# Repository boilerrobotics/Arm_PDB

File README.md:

# Arm_PDB
Power Distribution Board for our Robotic Arm
$ git init
$ git add -A
$ git commit -m 'Added my project'
$ git remote add origin git@github.com:MaggieM-Code/Power_Distribution_Board.git
$ git push -u -f origin main

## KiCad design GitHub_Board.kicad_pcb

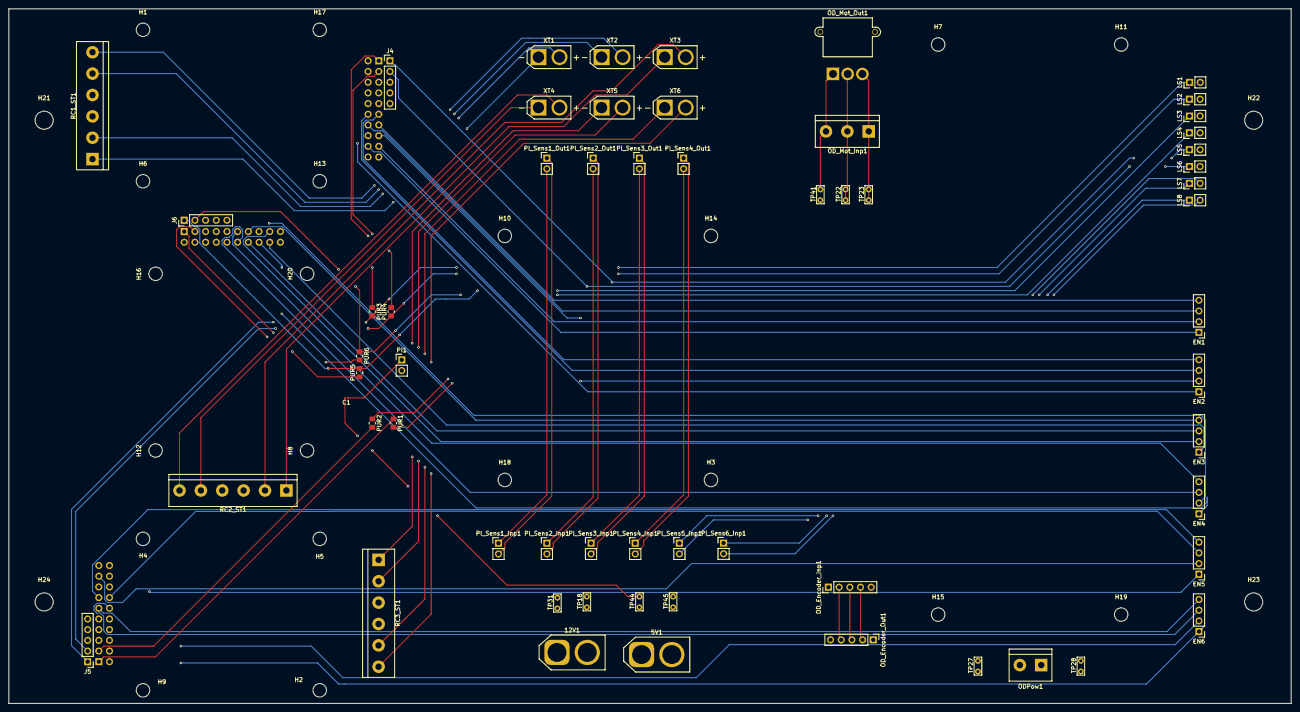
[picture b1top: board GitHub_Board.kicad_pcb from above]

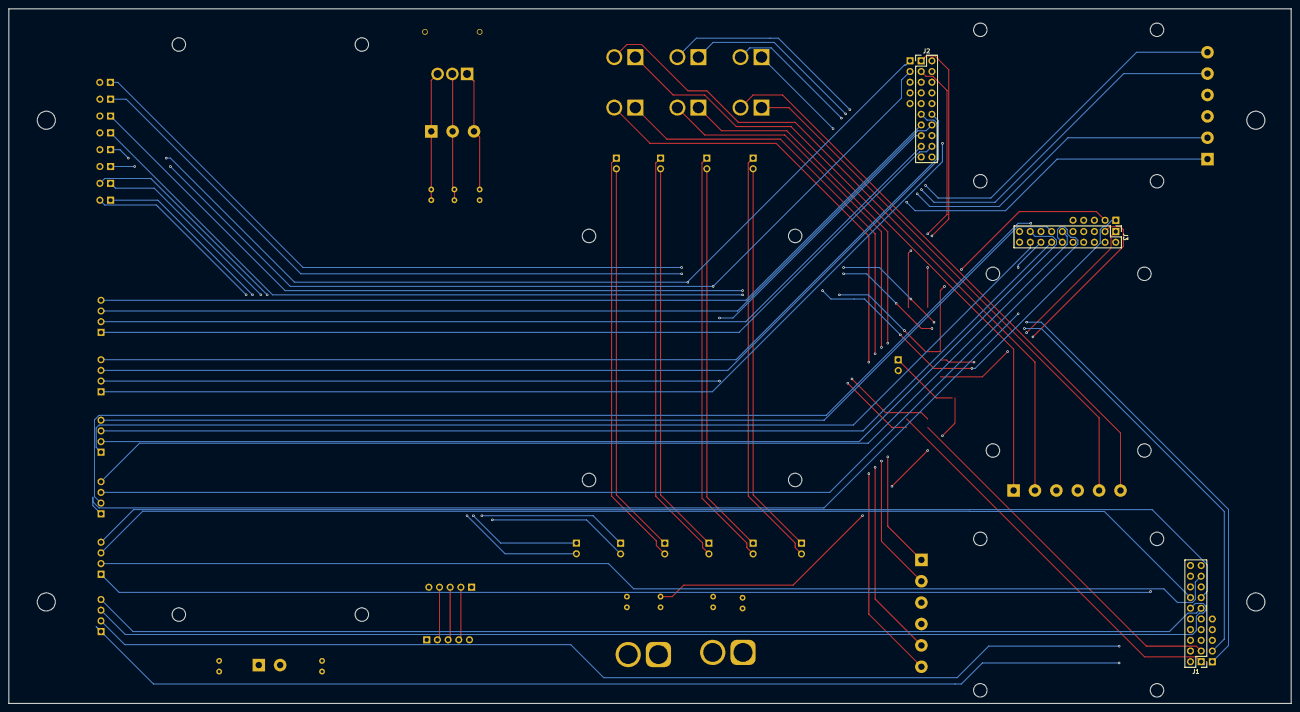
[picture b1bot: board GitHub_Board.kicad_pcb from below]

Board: 6 copper layers, 304.8 x 165.1 mm, 87 parts (3 on the bottom side), 70 nets.

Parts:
5V1, 12V1: Conn_01x02_Male; AMASS_XT60-M_1x02_P7.20mm_Vertical
C1: C; C_0201_0603Metric
EN1, EN2, EN3, EN4, EN5, EN6: Conn_01x04; PinHeader_1x04_P2.54mm_Vertical
H1, H2, H3, H4, H5, H6, H7, H8, H9, H10, H11, H12, H13, H14, H15, H16, H17, H18, H19, H20: MountingHole; MountingHole_3.2mm_M3
H21, H22, H23, H24: MountingHole; MountingHole_4.3mm_M4
J1, J2, J3: Conn_02x10_Top_Bottom; PinHeader_2x10_P2.54mm_Vertical
J4, J5, J6: Conn_01x05; PinHeader_1x05_P2.54mm_Vertical
LS1, LS2, LS3, LS4, LS5, LS6, LS7, LS8: Conn_02x01; PinHeader_1x02_P2.54mm_Vertical
ODPow1: Screw_Terminal_01x02; TerminalBlock_bornier-2_P5.08mm
OD_Encoder_Inp1: Conn_01x04; PinHeader_1x05_P2.54mm_Vertical
OD_Encoder_Out1: Conn_01x04; PinHeader_1x05_P2.54mm_Vertical
OD_Mot_Inp1: Screw_Terminal_01x03; TerminalBlock_bornier-3_P5.08mm
OD_Mot_Out1: Conn_01x03; AMASS_MR30PW-M_1x03_P3.50mm_Horizontal
PI1: Conn_01x02; PinHeader_1x02_P2.54mm_Vertical
PI_Sens1_Inp1, PI_Sens1_Out1, PI_Sens2_Inp1, PI_Sens2_Out1, PI_Sens3_Inp1, PI_Sens3_Out1, PI_Sens4_Inp1, PI_Sens4_Out1, PI_Sens5_Inp1, PI_Sens6_Inp1: Conn_01x02; PinHeader_1x02_P2.54mm_Vertical
PUR1, PUR2, PUR3, PUR4, PUR5, PUR6: R_US; R_0805_2012Metric_Pad1.20x1.40mm_HandSolder
RC1_ST1, RC2_ST1, RC3_ST1: Screw_Terminal_01x06; TerminalBlock_bornier-6_P5.08mm
TP18, TP22, TP23, TP27, TP28, TP31, TP41, TP44, TP45: TestPoint_Probe; TestPoint_Bridge_Pitch2.54mm_Drill0.7mm
XT1, XT2, XT3, XT4, XT5, XT6: Conn_01x02_Male; AMASS_XT30U-M_1x02_P5.0mm_Vertical

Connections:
+5V: 5V1.1, C1.2, OD_Encoder_Inp1.5, OD_Encoder_Out1.1, TP44.1
+12V: 12V1.1, ODPow1.2, RC1_ST1.3, RC2_ST1.3, RC3_ST1.3, TP27.1, TP31.1
/A: OD_Mot_Inp1.3, OD_Mot_Out1.1, TP41.1
/B: OD_Mot_Inp1.2, OD_Mot_Out1.2, TP22.1
/C: OD_Mot_Inp1.1, OD_Mot_Out1.3, TP23.1
/EN1+: EN1.2, J2.17
/EN1-: EN1.1, J2.18
/EN1a: EN1.4, J2.13
/EN1b: EN1.3, J2.14
/EN2+: EN2.2, J2.15
/EN2-: EN2.1, J2.16
/EN2a: EN2.4, J2.11
/EN2b: EN2.3, J2.12
/EN3+: EN3.2, J3.17
/EN3-: EN3.1, J3.18
/EN3a: EN3.4, J3.13
/EN3b: EN3.3, J3.14
/EN4+: EN4.2, J3.15
/EN4-: EN4.1, J3.16
/EN4a: EN4.4, J3.11
/EN4b: EN4.3, J3.12
/EN5+: EN5.2, J1.17
/EN5-: EN5.1, J1.18
/EN5a: EN5.4, J1.13
/EN5b: EN5.3, J1.14
/EN6+: EN6.2, J1.15
/EN6-: EN6.1, J1.16
/EN6a: EN6.4, J1.11
/EN6b: EN6.3, J1.12
/EN_A: OD_Encoder_Inp1.4, OD_Encoder_Out1.2
/EN_B: OD_Encoder_Inp1.3, OD_Encoder_Out1.3
/EN_C: OD_Encoder_Inp1.2, OD_Encoder_Out1.4
/LS1: J5.1, LS1.1, PUR3.2
/LS2: J5.2, LS2.1, PUR4.1
/LS3: J6.1, LS3.1, PUR5.2
/LS4: J6.2, LS4.1, PUR6.1
/LS5: J4.1, LS5.1, PUR1.2
/LS6: J4.2, LS6.1, PUR2.1
/LS7a: LS7.1, PI_Sens5_Inp1.1
/LS7b: LS7.2, PI_Sens5_Inp1.2
/LS8a: LS8.1, PI_Sens6_Inp1.1
/LS8b: LS8.2, PI_Sens6_Inp1.2
/Sens1_1: PI_Sens1_Inp1.2, PI_Sens1_Out1.1
/Sens1_2: PI_Sens1_Inp1.1, PI_Sens1_Out1.2
/Sens2_1: PI_Sens2_Inp1.2, PI_Sens2_Out1.1
/Sens2_2: PI_Sens2_Inp1.1, PI_Sens2_Out1.2
/Sens3_1: PI_Sens3_Inp1.2, PI_Sens3_Out1.1
/Sens3_2: PI_Sens3_Inp1.1, PI_Sens3_Out1.2
/Sens4_1: PI_Sens4_Inp1.2, PI_Sens4_Out1.1
/Sens4_2: PI_Sens4_Inp1.1, PI_Sens4_Out1.2
/XT301+: RC1_ST1.1, XT1.1
/XT301-: RC1_ST1.2, XT1.2
/XT302+: RC1_ST1.5, XT2.1
/XT302-: RC1_ST1.6, XT2.2
/XT303+: RC2_ST1.1, XT3.1
/XT303-: RC2_ST1.2, XT3.2
/XT304+: RC2_ST1.5, XT4.1
/XT304-: RC2_ST1.6, XT4.2
/XT305+: RC3_ST1.1, XT5.1
/XT305-: RC3_ST1.2, XT5.2
/XT306+: RC3_ST1.5, XT6.1
/XT306-: RC3_ST1.6, XT6.2
GND: 5V1.2, 12V1.2, J1.2, J1.4, J2.2, J2.4, J3.2, J3.4, LS1.2, LS2.2, LS3.2, LS4.2, LS5.2, LS6.2, ODPow1.1, OD_Encoder_Inp1.1, OD_Encoder_Out1.5, PI1.2, RC1_ST1.4, RC2_ST1.4, RC3_ST1.4, TP18.1, TP28.1, TP45.1
unnamed: J1.1, PUR1.1
unnamed: J1.3, PUR2.2
unnamed: J2.1, PUR3.1
unnamed: J2.3, PUR4.2
unnamed: J3.1, PUR5.1
unnamed: J3.3, PUR6.2
unnamed: C1.1, PI1.1

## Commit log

2024-11-20 Finished PDB.
2024-12-04 Adding Kicad files for the PDB.
2024-12-04 Added extra file.
2025-10-14 try1
